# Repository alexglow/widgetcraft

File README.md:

# widgetcraft
Arcane tech tools.

## ATtiny-dante – [project page](https://www.hackster.io/glowascii/attiny85-programmer-shield-for-arduino-uno-464d63)
An adapter to load Arduino code onto the ATtiny85 chip, using an Uno as the programmer, based on a circuit by [Arjun Ganesan](https://www.hackster.io/arjun/programming-attiny85-with-arduino-uno-afb829). The board art is a public-domain illustration, ["Geryon"](https://www.oldbookillustrations.com/illustrations/geryon/), from Dante's Inferno.

## Ouija ESP8266-01 programmer (ESProg) – [project page](https://www.hackster.io/glowascii/ouija-esp8266-programmer-d2c033)
An adapter to load Arduino code onto the ESP-01 module (ESP8266), using an FTDI cable, based on a circuit shared by Alasdair Allan in [Make Magazine](https://makezine.com/2015/04/01/installing-building-arduino-sketch-5-microcontroller/). The board art is partially traced from a public-domain illustration of [nasturtiums](https://www.oldbookillustrations.com/illustrations/nasturtium/), by Maurice Pillard Verneuil. It can be used as an earring, keychain fob, pendant, etc.

## Quarles' ruler
A PCB ruler designed to be produced using OSH Park's [After Dark](https://docs.oshpark.com/services/afterdark/) and Flex stack-ups. Featuring two public-domain images from [Quarles' Emblems](https://www.oldbookillustrations.com/titles/quarles-emblems/).

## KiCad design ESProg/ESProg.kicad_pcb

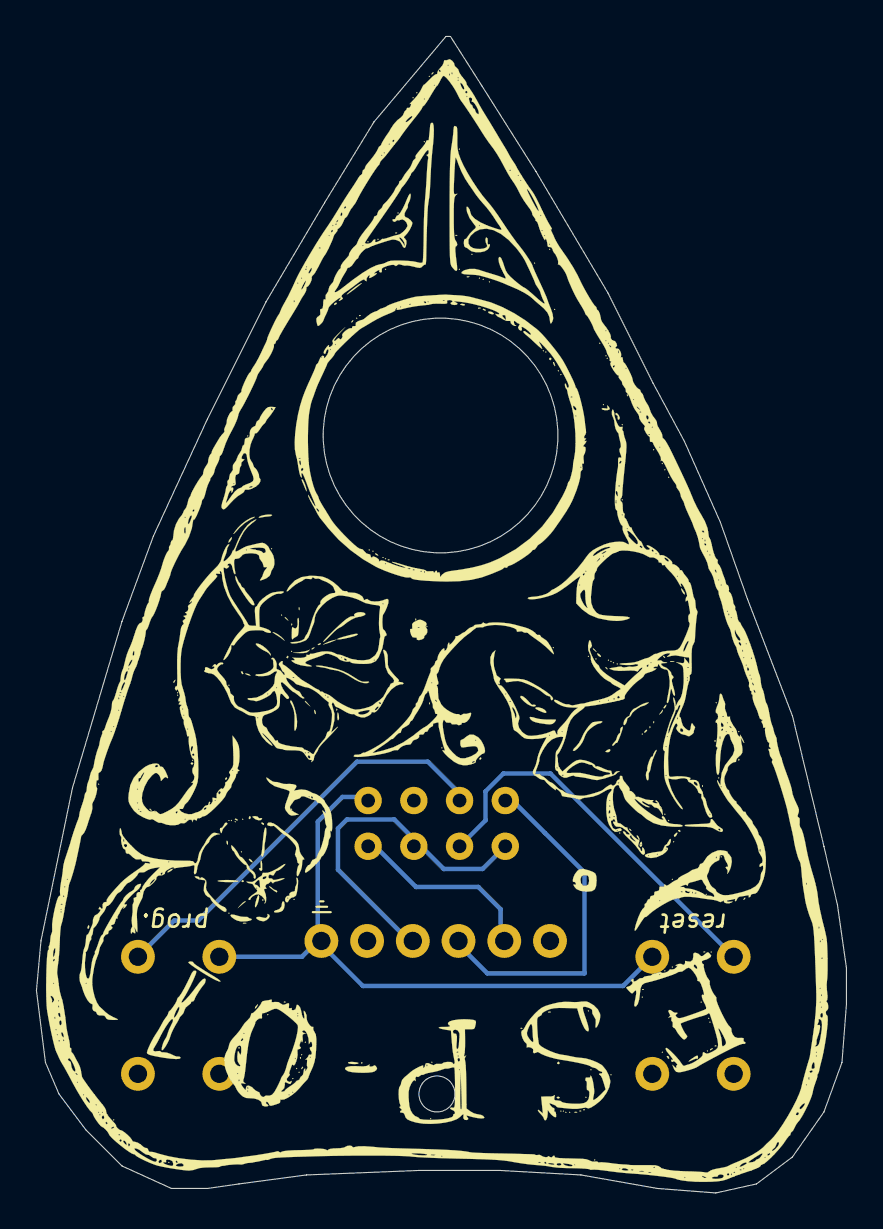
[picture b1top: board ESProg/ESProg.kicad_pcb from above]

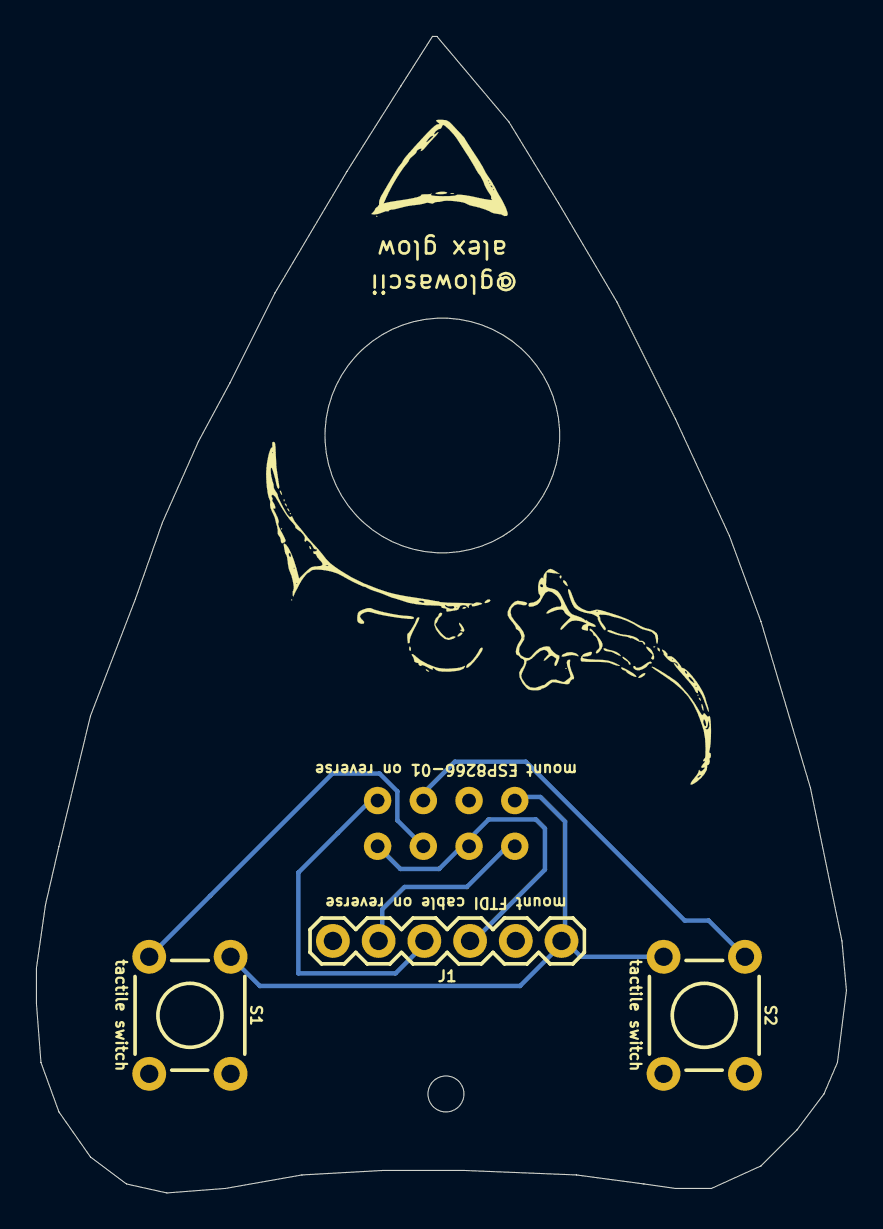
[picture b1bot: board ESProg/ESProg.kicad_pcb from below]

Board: 2 copper layers, 45.0 x 64.2 mm, 4 parts (2 on the bottom side), 6 nets.

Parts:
 : ESP8266-ESP-01; ESP-01
J1: FTDI_BASIC
S1, S2: tactile switch; TACTILE_SWITCH_PTH_6.0MM

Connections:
GND: .8, J1.GND, S1.1, S2.3
unnamed: .1, J1.RXI
unnamed: .5, J1.TXO
unnamed: .2, .4, J1.VCC
unnamed: .3, S1.3
unnamed: .6, S2.1

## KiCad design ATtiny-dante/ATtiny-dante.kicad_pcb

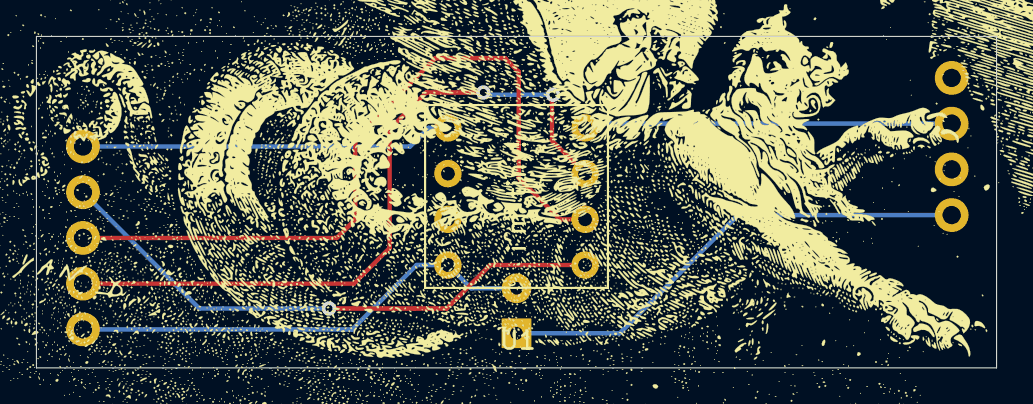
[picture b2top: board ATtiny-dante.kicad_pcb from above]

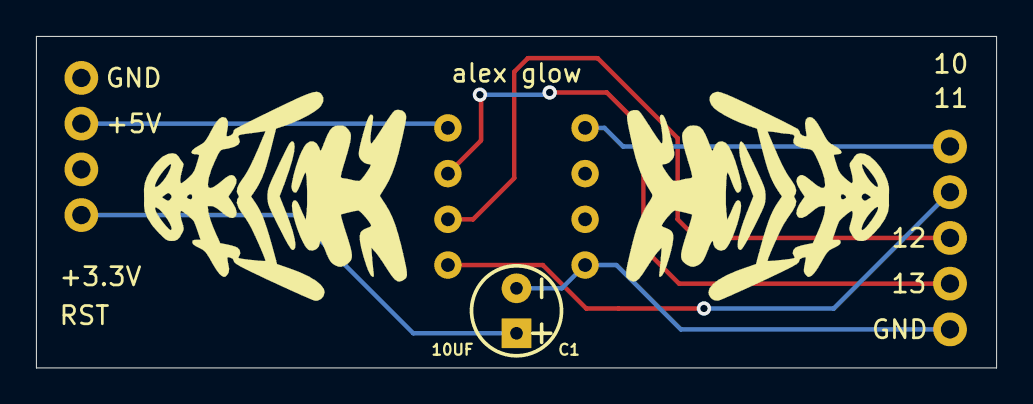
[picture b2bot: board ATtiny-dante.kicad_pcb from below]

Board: 2 copper layers, 53.3 x 18.4 mm, 5 parts (3 on the bottom side), 7 nets.

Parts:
 : atRsm
 #2: atLsm
B1: ARDUINO_UNO_R3_SHIELDBASIC; UNO_ATTINY_SHIELD
C1: 10UF; CPOL-RADIAL-2.5MM-5MM
U1: ATtiny85-DIP

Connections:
unnamed: B1.5V, U1.8
unnamed: B1.D10, U1.1
unnamed: B1.D11, U1.5
unnamed: B1.D12, U1.6
unnamed: B1.D13, U1.7
unnamed: B1.GND@, C1.2, U1.4
unnamed: B1.RES, C1.1

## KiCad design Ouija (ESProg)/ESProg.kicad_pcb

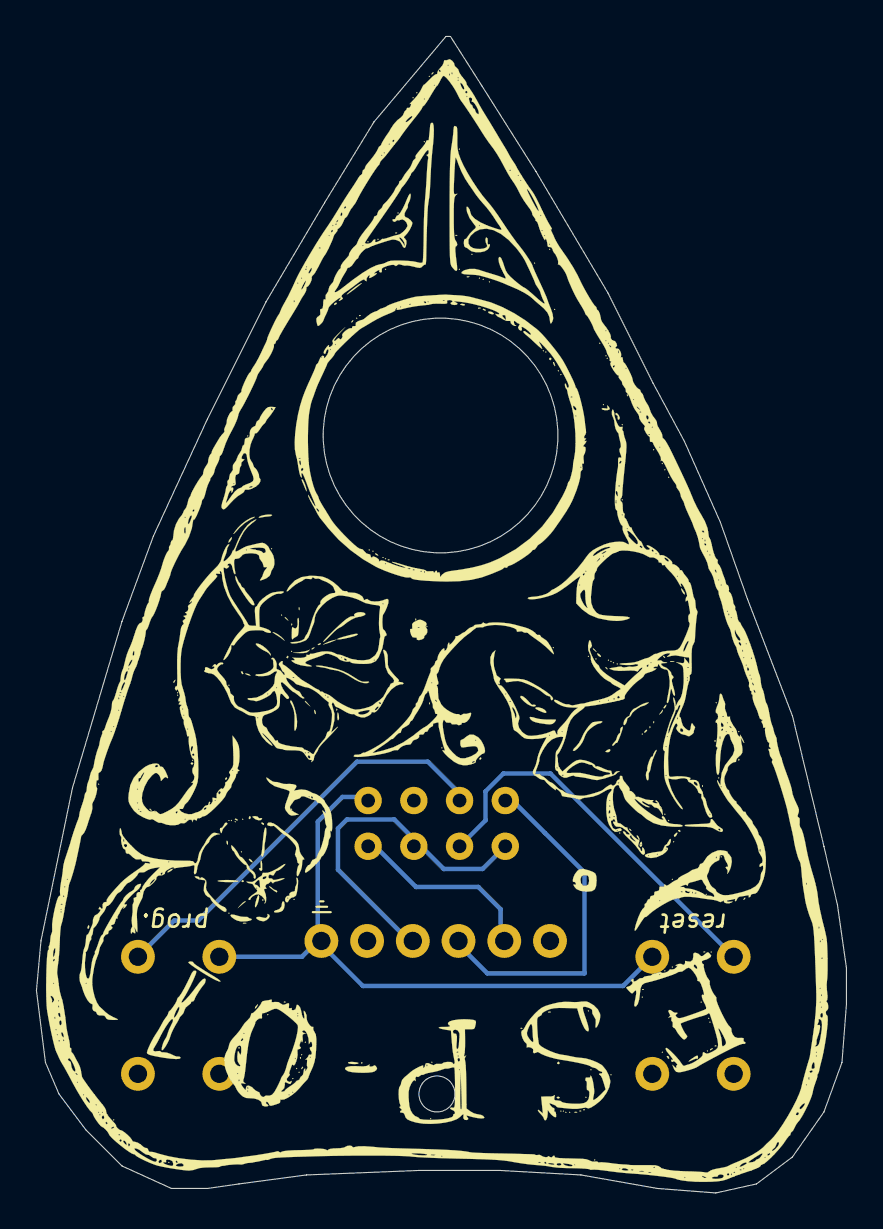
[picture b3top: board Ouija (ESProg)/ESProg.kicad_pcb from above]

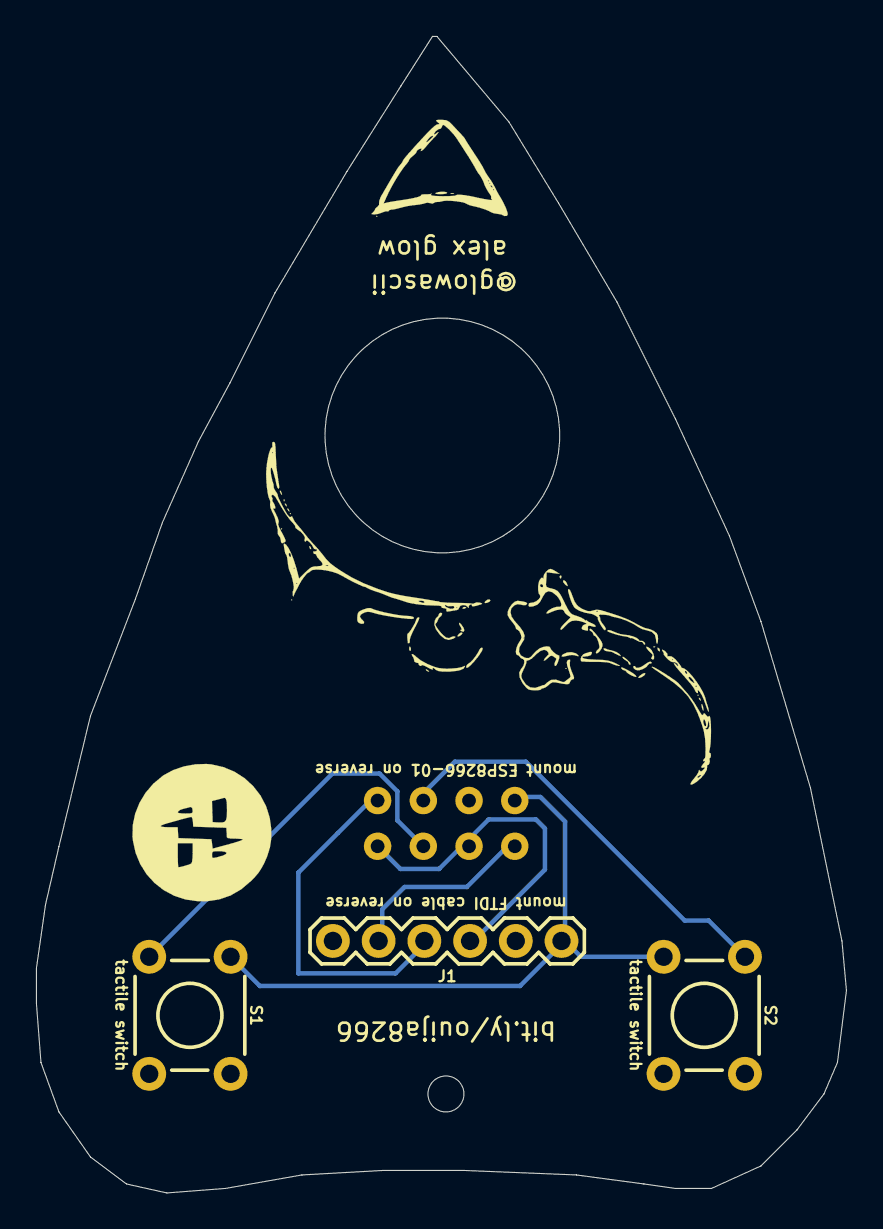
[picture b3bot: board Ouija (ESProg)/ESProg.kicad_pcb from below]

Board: 2 copper layers, 45.0 x 64.2 mm, 5 parts (3 on the bottom side), 6 nets.

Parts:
 : hlogoTiny
 #2: ESP8266-ESP-01; ESP-01
J1: FTDI_BASIC
S1, S2: tactile switch; TACTILE_SWITCH_PTH_6.0MM

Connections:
GND: #2.8, J1.GND, S1.1, S2.3
unnamed: #2.1, J1.RXI
unnamed: #2.5, J1.TXO
unnamed: #2.2, #2.4, J1.VCC
unnamed: #2.3, S1.3
unnamed: #2.6, S2.1

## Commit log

2021-03-09 add Quarles' Ruler
2021-03-10 add ATtiny-dante
2021-03-10 add ESProg
2021-10-28 Update with Hackster logo
2021-10-28 Adding Companion Core!
2021-10-28 Removing CCore
